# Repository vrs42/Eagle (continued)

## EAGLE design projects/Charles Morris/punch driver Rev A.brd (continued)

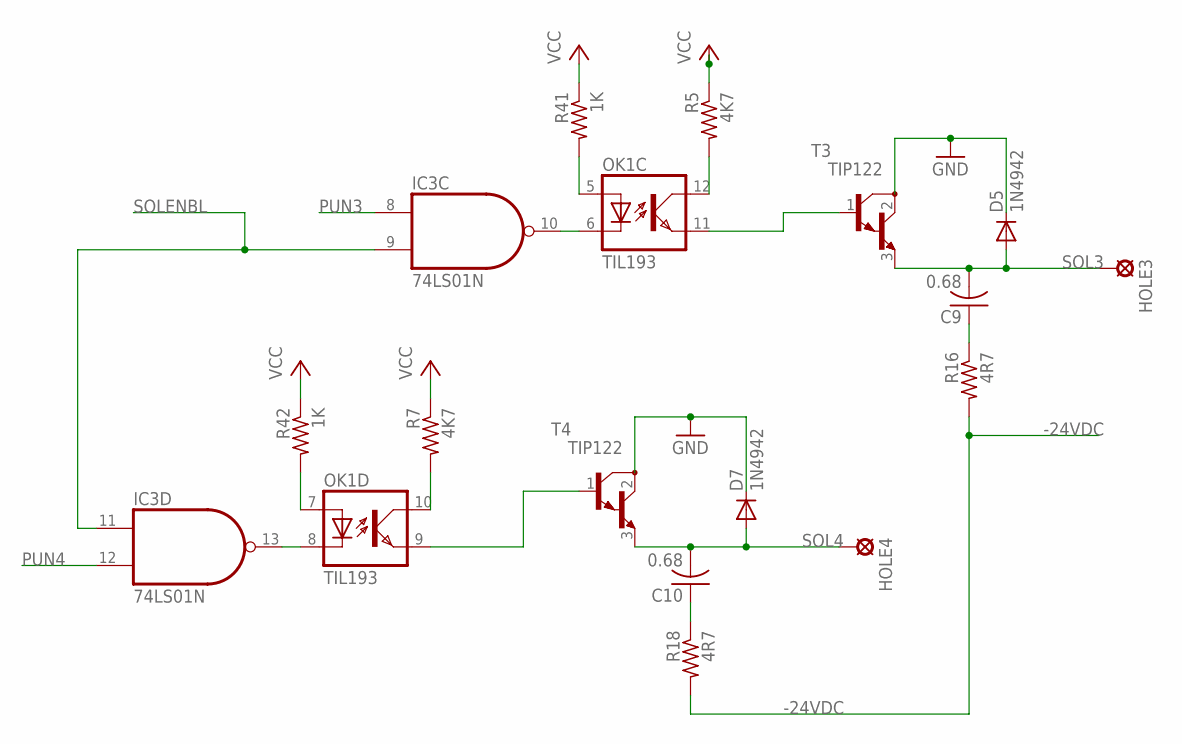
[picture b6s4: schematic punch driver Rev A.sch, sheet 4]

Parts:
C9, C10: 0.68; C075-042X103
D5, D7: 1N4942; DO41-10
HOLE3, HOLE4: SE13
IC3: 74LS01N; DIL14
OK1: TIL193; DIL16
R5, R7: 4K7; 0204/5
R16, R18: 4R7; 0207/10
R41, R42: 1K; 0204/5
T3, T4: TIP122; TO220

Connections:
-24VDC: R16.2, R18.2; also elsewhere on the board
GND: D5.C, D7.C, T3.2 (C), T4.2 (C); also elsewhere on the board
unnamed: OK1.12 (COL), R5.2
unnamed: OK1.10 (COL), R7.2
unnamed: C9.1, R16.1
unnamed: C10.1, R18.1
unnamed: IC3.10 (O), OK1.6 (C)
unnamed: IC3.13 (O), OK1.8 (C)
unnamed: OK1.7 (A), R42.2
unnamed: OK1.5 (A), R41.2
unnamed: OK1.9 (EMIT), T4.1 (B)
unnamed: OK1.11 (EMIT), T3.1 (B)
PUN3: IC3.8 (I0); also elsewhere on the board
PUN4: IC3.12 (I1); also elsewhere on the board
SOL3: C9.2, D5.A, HOLE3.MP, T3.3 (E)
SOL4: C10.2, D7.A, HOLE4.MP, T4.3 (E)
SOLENBL: IC3.9 (I1), IC3.11 (I0); also elsewhere on the board
VCC: R5.1, R7.1, R41.1, R42.1; also elsewhere on the board

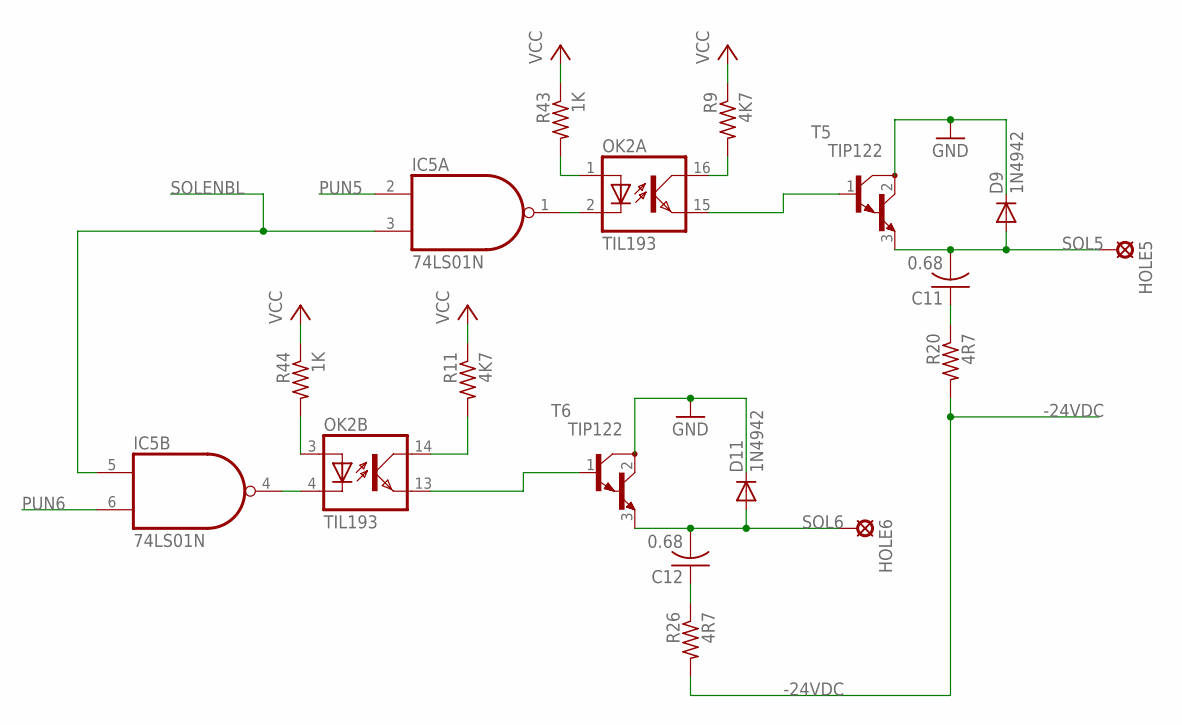
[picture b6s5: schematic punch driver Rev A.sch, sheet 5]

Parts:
C11, C12: 0.68; C075-042X103
D9, D11: 1N4942; DO41-10
HOLE5, HOLE6: SE13
IC5: 74LS01N; DIL14
OK2: TIL193; DIL16
R9, R11: 4K7; 0204/5
R20, R26: 4R7; 0207/10
R43, R44: 1K; 0204/5
T5, T6: TIP122; TO220

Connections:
-24VDC: R20.2, R26.2; also elsewhere on the board
GND: D9.C, D11.C, T5.2 (C), T6.2 (C); also elsewhere on the board
unnamed: OK2.14 (COL), R11.2
unnamed: OK2.16 (COL), R9.2
unnamed: C11.1, R20.1
unnamed: C12.1, R26.1
unnamed: IC5.1 (O), OK2.2 (C)
unnamed: IC5.4 (O), OK2.4 (C)
unnamed: OK2.3 (A), R44.2
unnamed: OK2.1 (A), R43.2
unnamed: OK2.13 (EMIT), T6.1 (B)
unnamed: OK2.15 (EMIT), T5.1 (B)
PUN5: IC5.2 (I0); also elsewhere on the board
PUN6: IC5.6 (I1); also elsewhere on the board
SOL5: C11.2, D9.A, HOLE5.MP, T5.3 (E)
SOL6: C12.2, D11.A, HOLE6.MP, T6.3 (E)
SOLENBL: IC5.3 (I1), IC5.5 (I0); also elsewhere on the board
VCC: R9.1, R11.1, R43.1, R44.1; also elsewhere on the board

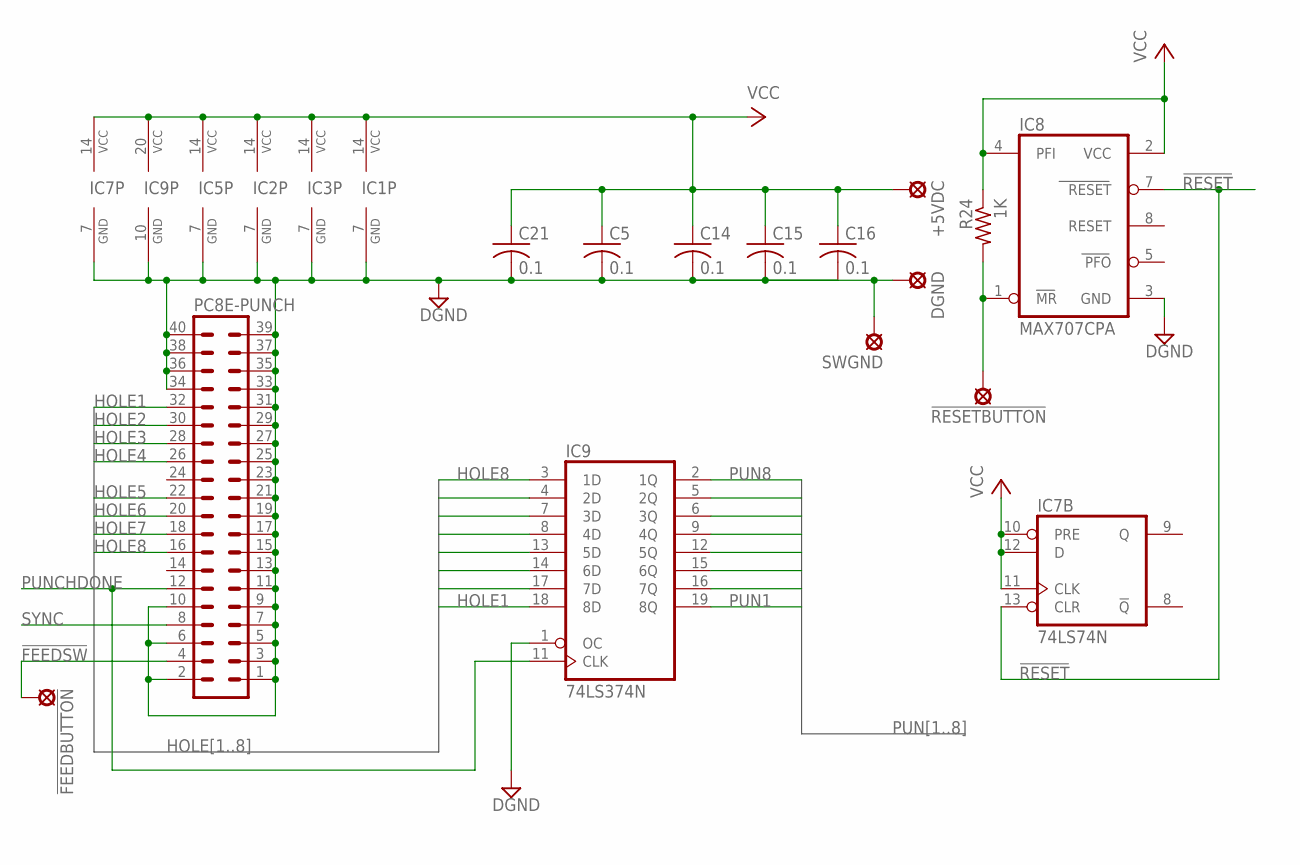
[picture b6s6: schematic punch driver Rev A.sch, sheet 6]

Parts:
!FEEDBUTTON: SE13
!RESETBUTTON: SE13
+5VDC: SE13
C5, C14, C15, C16, C21: 0.1; C050-025X075
DGND: SE13
IC1, IC2: 74121N; DIL14
IC3, IC5: 74LS01N; DIL14
IC7: 74LS74N; DIL14
IC8: MAX707CPA; DIL08
IC9: 74LS374N; DIL20
PC8E-PUNCH: MA20-2
R24: 1K; 0204/5
SWGND: SE13

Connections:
!FEEDSW: !FEEDBUTTON.MP, PC8E-PUNCH.4
!RESET: IC7.13 (CLR), IC8.7 (RESET); also elsewhere on the board
DGND: C5.2, C14.2, C15.2, C16.2, C21.2, DGND.MP, IC1.7 (GND), IC2.7 (GND), IC3.7 (GND), IC5.7 (GND), IC7.7 (GND), IC8.3 (GND), IC9.1 (OC), IC9.10 (GND), PC8E-PUNCH.1, PC8E-PUNCH.2, PC8E-PUNCH.3, PC8E-PUNCH.5, PC8E-PUNCH.6, PC8E-PUNCH.7, PC8E-PUNCH.9, PC8E-PUNCH.10, PC8E-PUNCH.11, PC8E-PUNCH.13, PC8E-PUNCH.15, PC8E-PUNCH.17, PC8E-PUNCH.19, PC8E-PUNCH.21, PC8E-PUNCH.23, PC8E-PUNCH.25, PC8E-PUNCH.27, PC8E-PUNCH.29, PC8E-PUNCH.31, PC8E-PUNCH.33, PC8E-PUNCH.34, PC8E-PUNCH.35, PC8E-PUNCH.36, PC8E-PUNCH.37, PC8E-PUNCH.38, PC8E-PUNCH.39, PC8E-PUNCH.40, SWGND.MP; also elsewhere on the board
HOLE1: IC9.18 (8D), PC8E-PUNCH.32
HOLE2: IC9.17 (7D), PC8E-PUNCH.30
HOLE3: IC9.14 (6D), PC8E-PUNCH.28
HOLE4: IC9.13 (5D), PC8E-PUNCH.26
HOLE5: IC9.8 (4D), PC8E-PUNCH.22
HOLE6: IC9.7 (3D), PC8E-PUNCH.20
HOLE7: IC9.4 (2D), PC8E-PUNCH.18
HOLE8: IC9.3 (1D), PC8E-PUNCH.16
unnamed: !RESETBUTTON.MP, IC8.1 (MR), R24.2
PUN1: IC9.19 (8Q); also elsewhere on the board
PUN2: IC9.16 (7Q); also elsewhere on the board
PUN3: IC9.15 (6Q); also elsewhere on the board
PUN4: IC9.12 (5Q); also elsewhere on the board
PUN5: IC9.9 (4Q); also elsewhere on the board
PUN6: IC9.6 (3Q); also elsewhere on the board
PUN7: IC9.5 (2Q); also elsewhere on the board
PUN8: IC9.2 (1Q); also elsewhere on the board
PUNCHDONE: IC9.11 (CLK), PC8E-PUNCH.12; also elsewhere on the board
SYNC: PC8E-PUNCH.8; also elsewhere on the board
VCC: +5VDC.MP, C5.1, C14.1, C15.1, C16.1, C21.1, IC1.14 (VCC), IC2.14 (VCC), IC3.14 (VCC), IC5.14 (VCC), IC7.10 (PRE), IC7.11 (CLK), IC7.12 (D), IC7.14 (VCC), IC8.2 (VCC), IC8.4 (PFI), IC9.20 (VCC), R24.1; also elsewhere on the board

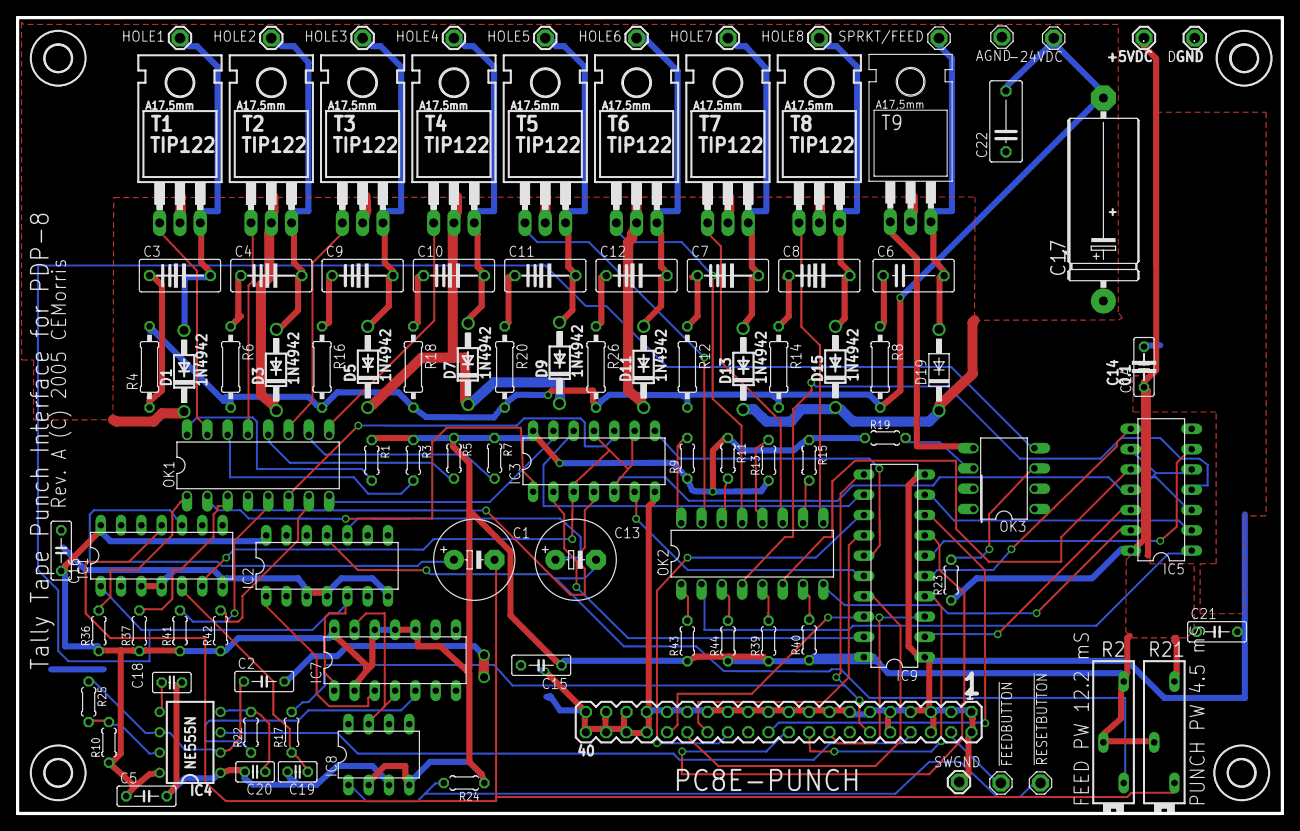
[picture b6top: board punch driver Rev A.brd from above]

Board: 2 copper layers, 158.3 x 99.6 mm, 106 parts (0 on the bottom side), 91 nets.

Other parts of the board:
U$1, U$2, U$3, U$4: 3,3

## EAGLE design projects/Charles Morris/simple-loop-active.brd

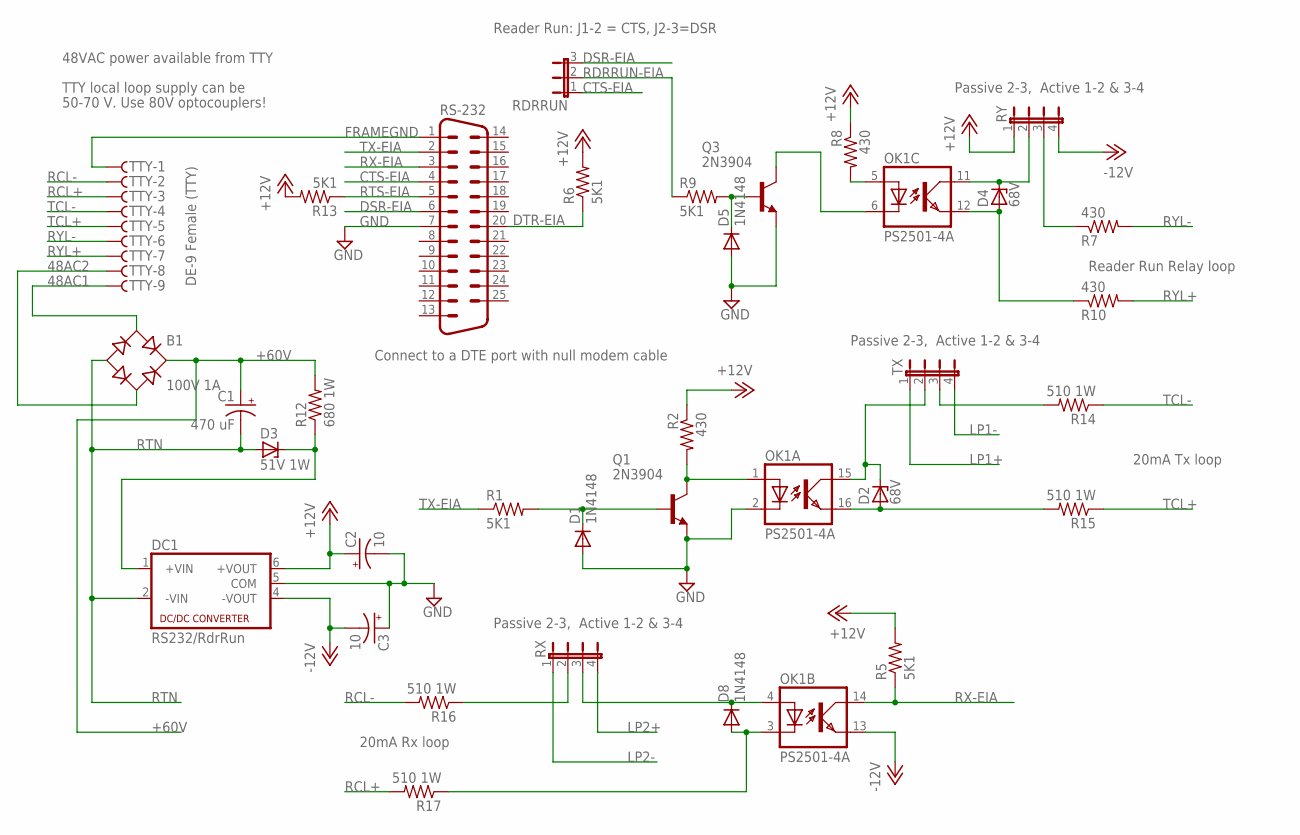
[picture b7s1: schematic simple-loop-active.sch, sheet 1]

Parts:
B1: 100V 1A; RB1A
C1: 470 uF; E7,5-18
C2, C3: 10; B45181A
D1, D5, D8: 1N4148; DO35-10
D2, D4: 68V; DO41Z10
D3: 51V 1W; DO41Z10
DC1: RS232/RdrRun; NMA
OK1: PS2501-4A; DIL16
Q1, Q3: 2N3904; TO92
R1, R5, R6, R9, R13: 5K1; 0207/10
R2, R7, R8, R10: 430; 0207/10
R12: 680 1W; P0817V
R14, R15, R16, R17: 510 1W; P0817V
RDRRUN: JP2E; JP2
RS-232: M25H
RX: JP4E; JP4
RY: JP4E; JP4
TTY: F09HS; F09H
TX: JP4E; JP4

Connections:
48AC1: B1.AC1, TTY.9
48AC2: B1.AC2, TTY.8
+12V: C2.+, DC1.6 (+VOUT), R2.1, R5.2, R6.2, R8.1, R13.2, RY.1
+48VDC: D3.C, DC1.1 (+VIN), R12.1
+60V: B1.+, C1.+, R12.2; also elsewhere on the board
-12V: C3.-, DC1.4 (-VOUT), OK1.13 (EMIT), RY.4
CTS-EIA: RDRRUN.1, RS-232.4
DSR-EIA: RDRRUN.3, RS-232.6
DTR-EIA: R6.1, RS-232.20
FRAMEGND: RS-232.1, TTY.1
GND: C2.-, C3.+, D1.A, D5.A, DC1.5 (COM), OK1.2 (C), Q1.3 (E), Q3.3 (E), RS-232.7
LP1+: TX.1; also elsewhere on the board
LP1-: TX.4; also elsewhere on the board
LP2+: RX.4; also elsewhere on the board
LP2-: RX.1; also elsewhere on the board
unnamed: D8.C, OK1.4 (A), RX.3
unnamed: R16.1, RX.2
unnamed: D8.A, OK1.3 (C), R17.1
unnamed: D2.A, OK1.16 (EMIT), R15.2
unnamed: OK1.5 (A), R8.2
unnamed: D2.C, OK1.15 (COL), TX.2
unnamed: D1.C, Q1.2 (B), R1.2
unnamed: D4.C, OK1.11 (COL), RY.2
unnamed: OK1.1 (A), Q1.1 (C), R2.2
unnamed: D4.A, OK1.12 (EMIT), R10.1
unnamed: R7.1, RY.3
unnamed: OK1.6 (C), Q3.1 (C)
unnamed: D5.C, Q3.2 (B), R9.2
unnamed: R14.2, TX.3
RCL+: R17.2, TTY.3
RCL-: R16.2, TTY.2
RDRRUN-EIA: R9.1, RDRRUN.2
RTN: B1.-, C1.-, D3.A, DC1.2 (-VIN); also elsewhere on the board
RTS-EIA: R13.1, RS-232.5
RX-EIA: OK1.14 (COL), R5.1, RS-232.3
RYL+: R10.2, TTY.7
RYL-: R7.2, TTY.6
TCL+: R15.1, TTY.5
TCL-: R14.1, TTY.4
TX-EIA: R1.1, RS-232.2

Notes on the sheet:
TTY local loop supply can be
50-70 V. Use 80V optocouplers!
20mA Tx loop
20mA Rx loop
48VAC power available from TTY
Reader Run Relay loop
Connect to a DTE port with null modem cable
Passive 2-3, Active 1-2 & 3-4
DE-9 Female (TTY)
Reader Run: J1-2 = CTS, J2-3=DSR

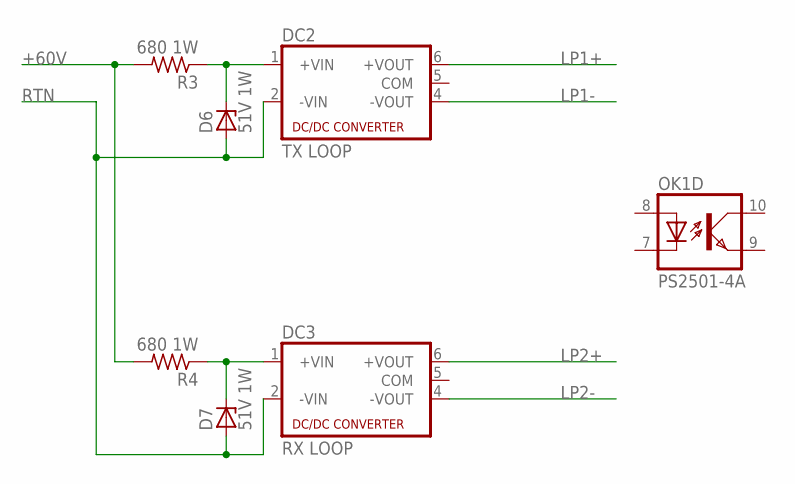
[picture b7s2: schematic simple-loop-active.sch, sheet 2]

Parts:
D6, D7: 51V 1W; DO41Z10
DC2: TX LOOP; NMA
DC3: RX LOOP; NMA
OK1: PS2501-4A; DIL16
R3, R4: 680 1W; P0817V

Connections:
+48VDC1: D6.C, DC2.1 (+VIN), R3.1
+48VDC2: D7.C, DC3.1 (+VIN), R4.1
+60V: R3.2, R4.2; also elsewhere on the board
LP1+: DC2.6 (+VOUT); also elsewhere on the board
LP1-: DC2.4 (-VOUT); also elsewhere on the board
LP2+: DC3.6 (+VOUT); also elsewhere on the board
LP2-: DC3.4 (-VOUT); also elsewhere on the board
RTN: D6.A, D7.A, DC2.2 (-VIN), DC3.2 (-VIN); also elsewhere on the board

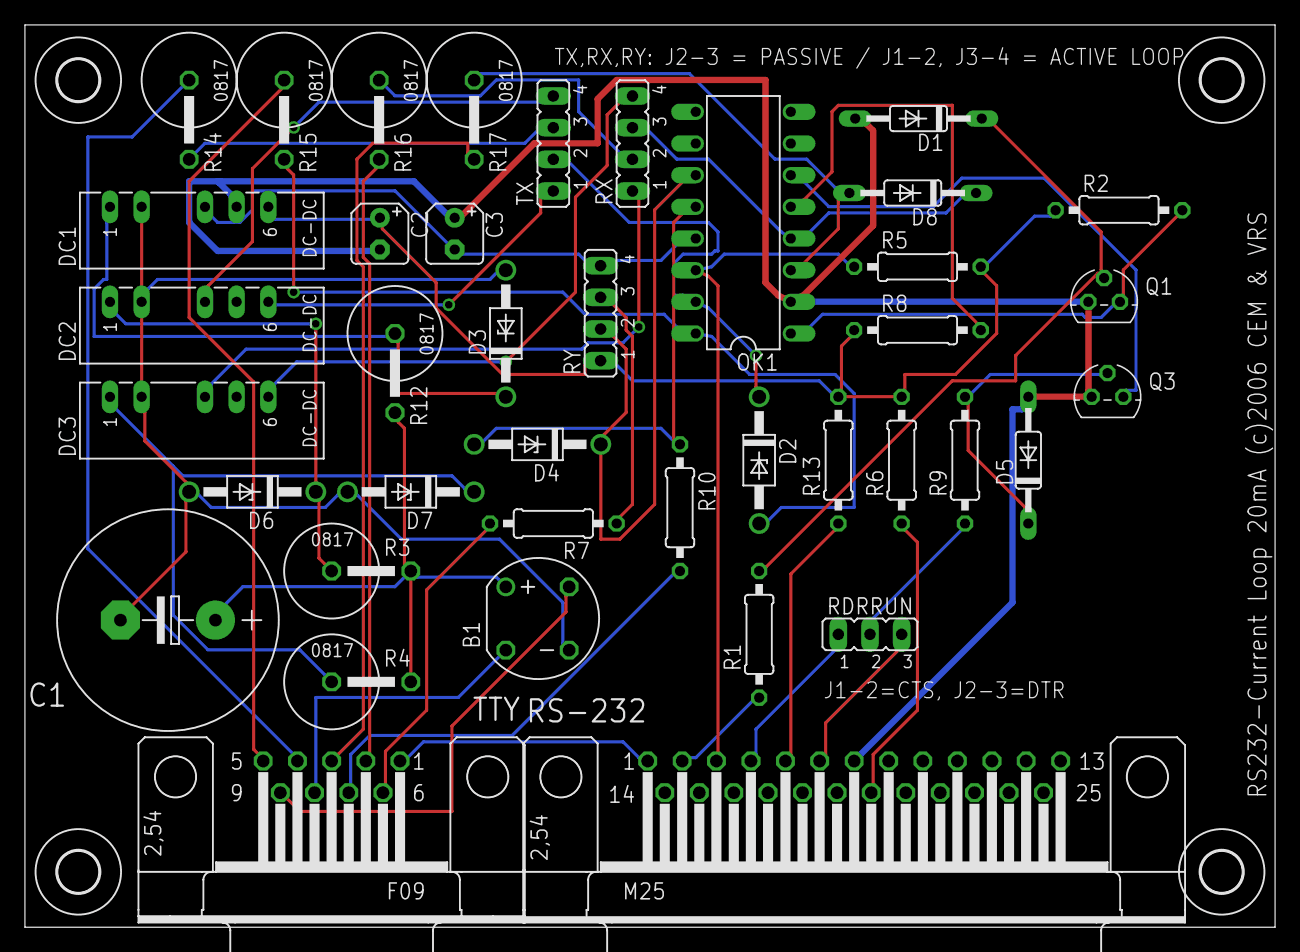
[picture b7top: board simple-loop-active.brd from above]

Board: 2 copper layers, 100.3 x 72.4 mm, 44 parts (0 on the bottom side), 42 nets.

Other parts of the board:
U$1, U$2, U$3, U$4: 3,3
